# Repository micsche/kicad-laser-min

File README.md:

## kicad-laser-min

The application will take a PCB file generated by KICAD and create paths isolating all nets.
This is isolation routing for PCBs.

### Operation
The application uses a line Voronoi segmentation technique on the BW image of one layer of PCB. The Voronoi algorithm has been implemented in C++
by colorizing each track a different color. Each track is dilated until regions meet. Finally, an edge detection algorithm will produce the contours.
The contours produce the PCB region isolation. A contour following algorithm will transform the edge into gcode.

Double separation creates increase isolation between PCB tracks  (0.5mm per contour) .

The KICAD pcb to image conversion uses `<pxmm>` scale (which defaults to 30 pixels per mm).

Edge dilation takes time (why it is implemented in C++). The time is dependant on the `<pxmm>` scale.

Drill holes for pads and vias will be added to the end gcode. The holes drawn will be original size.

From left to right - BW Image of tracks, Colourized Dilation of tracks, Edge Detection of dilation.

## Note
The application is provided as is. I tested it with my own generated pcbs and worked well. However, your testing is also appreciated.
Please review outputs, especially gcode (as I am not an expert on any of the file formats used).

```KICAD Version used :
    Application: Pcbnew
    Version: 5.1.6-c6e7f7d~86~ubuntu18.04.1, release build
```

### Usage

```Usage:
Option: -m         Process map.png directly
        -f         Process Front Copper Layer.
        -b         Process Bottom and Front Copper Layer.
        -c         Do not cleanup after processing.
        -p<pxmm>   Change pixels per mm (default 30)
        -v        Don't Double Mark Vias
        -x        Mark Pads and Vias with '+'
        -d        Increase Separation between Isolated Zones
        -t       Increase Separation between Isolated Zones but include middle-trace
        -r       Override feedrate (default 120)

```

### Files
kicadpcb2contour.cpp

### Output Files
    map.png       - BW output image of Kicad PCB conversion
    cpp_image.png - your mind on LSD. The colorised image dilation of PCB tracks.
    trace.png     - Edge detection of the dilated image
    front.gcode   - Final gcode for Front Layer
    bottom.gcode  - Final gcode for Bottom Layer
    mask.png      - Mask of PCB to handle Edge cuts

### Dependencies
OpenCV libraries (version 4.5 used) with opencv_contrib (ximgproc)

### Compilation
Go into the directory and type in ```make```.

### Solved
Some offshoot tracks where created, output from opencv finContours. Contours outside the board are pruned out.

### Errors

However, as shown the inter-contour distance tolerance is of 0.0685mm. I have a laser cutter with an engraving width of 0.2mm (i.e. a
possible 0.1mm engraving width on the centre of track to a track coninciding from left or right side)

Contours do not touch.

However, distance is small enough to still function.

OpenCV follow contours creates two contours from both sides.
One could propose new findcontour method. No real problem here, rather than double time to process pcb.

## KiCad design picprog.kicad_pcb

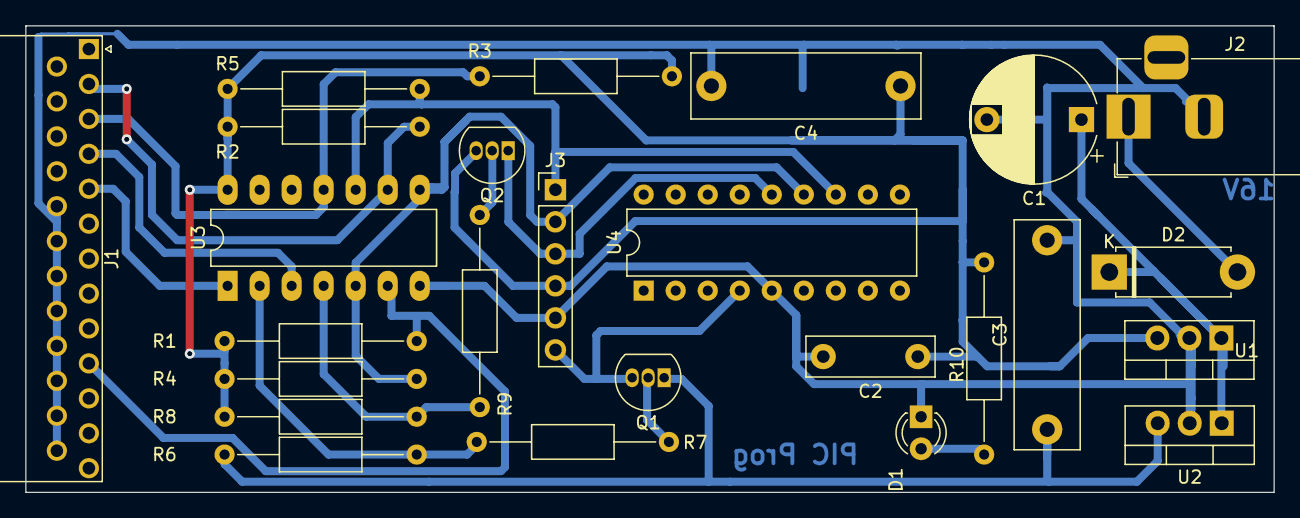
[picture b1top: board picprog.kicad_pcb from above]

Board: 2 copper layers, 99.0 x 37.0 mm, 25 parts (0 on the bottom side), 19 nets.

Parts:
C1: 100uF; CP_Radial_D10.0mm_P7.50mm
C2: 0.1; C_Rect_L10.0mm_W3.0mm_P7.50mm_FKS3_FKP3
C3, C4: 0.1u; C_Rect_L18.0mm_W5.0mm_P15.00mm_FKS3_FKP3
D1: LED; LED_D3.0mm
D2: 1n4001; D_5W_P10.16mm_Horizontal
J1: DB25_Male; DSUB-25_Male_Horizontal_P2.77x2.54mm_EdgePinOffset9.40mm
J2: Jack-DC; BarrelJack_Horizontal
J3: Conn_01x06_Female; PinHeader_1x06_P2.54mm_Vertical
Q1, Q2: 2N3906; TO-92_Inline
R1, R2, R3, R4, R5, R6, R8: 10k; R_Axial_DIN0207_L6.3mm_D2.5mm_P15.24mm_Horizontal
R7, R9: 1k; R_Axial_DIN0207_L6.3mm_D2.5mm_P15.24mm_Horizontal
R10: 330; R_Axial_DIN0207_L6.3mm_D2.5mm_P15.24mm_Horizontal
U1: L7805; TO-220-3_Vertical
U2: LM7812_TO220; TO-220-3_Vertical
U3: 7407; DIP-14_W7.62mm_LongPads
U4: PIC16F84-XXP; DIP-18_W7.62mm

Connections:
+5V: C2.1, C4.1, J3.4, Q2.3, R1.2, R2.2, R3.2, R4.1, R5.2, R8.1, R10.2, U1.3, U3.14
+12V: C3.1, Q1.3, R6.1, U2.3
GND: C1.2, C2.2, C3.2, C4.2, D1.1, J1.18, J1.19, J1.20, J1.21, J1.22, J1.23, J1.24, J1.25, J2.2, J3.5, U1.2, U2.2, U3.7, U4.5
LP2: J1.2, R2.1, U3.9
LP3: J1.3, R3.1, U3.11
LP4: J1.4, U3.3
LP5: J1.5, U3.1
LP10: J1.10, R1.1, U3.6
MCLR: J3.6, Q1.1, U4.4
unnamed: D1.2, R10.1
unnamed: D2.2, J2.1
unnamed: Q1.2, R7.1
unnamed: Q2.2, R9.1
unnamed: R6.2, R7.2, U3.2
unnamed: R8.2, R9.2, U3.4
RB6: J3.1, R5.1, U3.10, U4.12
RB7: J3.2, R4.2, U3.5, U3.8, U4.13
VDC: C1.1, D2.1, U1.1, U2.1
VDD: J3.3, Q2.1, U4.14

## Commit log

2020-02-20 File v0.1
    laser paths between tracks created
    Paths leading nowhere eliminated
2020-02-20 v.11
2020-02-20 v0.12
2020-02-20 PCB import
2020-02-20 Test erode-dilate
2020-02-21 v.12
    Small lengths removed
    Endpoint of large lengths stored
2020-02-27 Algo4
2020-03-15 mar12
2020-04-05 ordered list output
2020-05-07 v0.20
    TODO: Pads, CVIMAGE standalone
2020-05-07 v0.21
    TODO: CVIMAGE Standalone, write holes in end Python Script
2020-05-11 v0.22
    TODO
2020-05-13 V0.23
    No redundant
2020-05-15 CPP
    moving to pure CPP
2020-07-11 Final v1.0
    C++
2020-07-11 Final v1.1
2020-07-11 v1.2
2020-07-11 v1.3
2020-07-11 v1.4
2020-07-11 v1.31
2020-07-11 v1.32
2020-07-11 v1.33
2020-07-12 V1.34
2020-07-12 v.134.1
2020-07-12 v.134.2
2020-07-14 v.134.3
2020-07-14 v.134,4
2020-07-14 v.134.4
2020-08-01 Handled Rounded Rectangles
    Rounded rectangles could touch tracks if drawn as rectangles. Elllipses are smaller than rounded rectangles but touch all the X and Y dimensions.
2020-08-10 Edge Cuts
    Now the tracer will handle non-rectangular cuts
2020-08-10 Edge Cuts
    Handles PCB with Edge Cuts
2020-08-11 Modified Rotated
    Rotated pads correction
2020-08-11 Edge Cuts
    ARC Edge cuts - partial solve - test required
2020-08-12 Rounded Rectangle Holes
    Oval holes complete.
2020-08-13 RR Holes
    Modify test
2020-08-19 Correct Flip
    Bottom and Front are flipped
2020-08-20 Make file
    make
2020-08-20 Make file
    Readme
2020-09-13 Issue Solved
    Small partitions were left out of final gcode
2020-09-15 Improved Line Shaping
2020-11-30 Double contouring
    Increase track separation
2020-11-30 Double contouring 1.1
    Increase track separation
2020-11-30 Double contouring 1.11
2020-12-06 Via Mark
    Option to Mark Vias
2021-04-14 Correction on SMD
2021-08-07 Restart
    Linerize 1.0
2021-08-12 Major Mods
    1. Override feedrate feature
    2. Prune offshoot tracks
    3. New mode with increase separation
    4. New mode with increase separation and mid track
    5. Mark pads/vias with '+' instead (aids drilling)
